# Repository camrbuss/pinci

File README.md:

# pinci the keyboard 🦐

*pinci pinches panic like popcorn*

This project is still under development, submit an issue if you have questions.

## Hardware

- 34 key layout with two thumb keys skewed outward
- [Kailh PG1232](https://www.kailhswitch.com/news/pg1232-keyboard-switch-brief-introduction-21834938.html) Low Profile Switches
- [Raspberry Pi Pico](https://www.raspberrypi.org/products/raspberry-pi-pico/) (RP2040)
- Reversible PCB
- TRS capable hardware (normal headphone cable)
- Minimal SMD components and no THT components
- No diodes, just direct switch to gpio connections
- Useable with and without a case

### BOM

| Part | Qty | Manufacturer Part No |
| ---- | --- | -------------------- |
| Kailh Swithces | 34 | PG1232 |
| Raspberry Pi Pico | 2 | SC0915 |
| 1206 5% 10k Ohm Resistor | 2 | N/A |
| 3.5mm Headphone Jack | 2 | 54-00177 |

## Firmware

The [firmware](https://github.com/camrbuss/pinci/blob/main/firmware/src/main.rs) is writen in Rust using the following (and more) libraries

- [Keyberon](https://github.com/TeXitoi/keyberon)
- [RTIC](https://github.com/rtic-rs/cortex-m-rtic)
- [rp2040-hal](https://github.com/rp-rs/rp-hal/tree/main/rp2040-hal)

## Inspiration

Thanks to all the open-source projects that have inspired this project

- [Ferris](https://github.com/pierrechevalier83/ferris)
- [Fifi](https://github.com/raychengy/fifi_split_keeb)
- [KeySeeBee](https://github.com/TeXitoi/keyseebee)

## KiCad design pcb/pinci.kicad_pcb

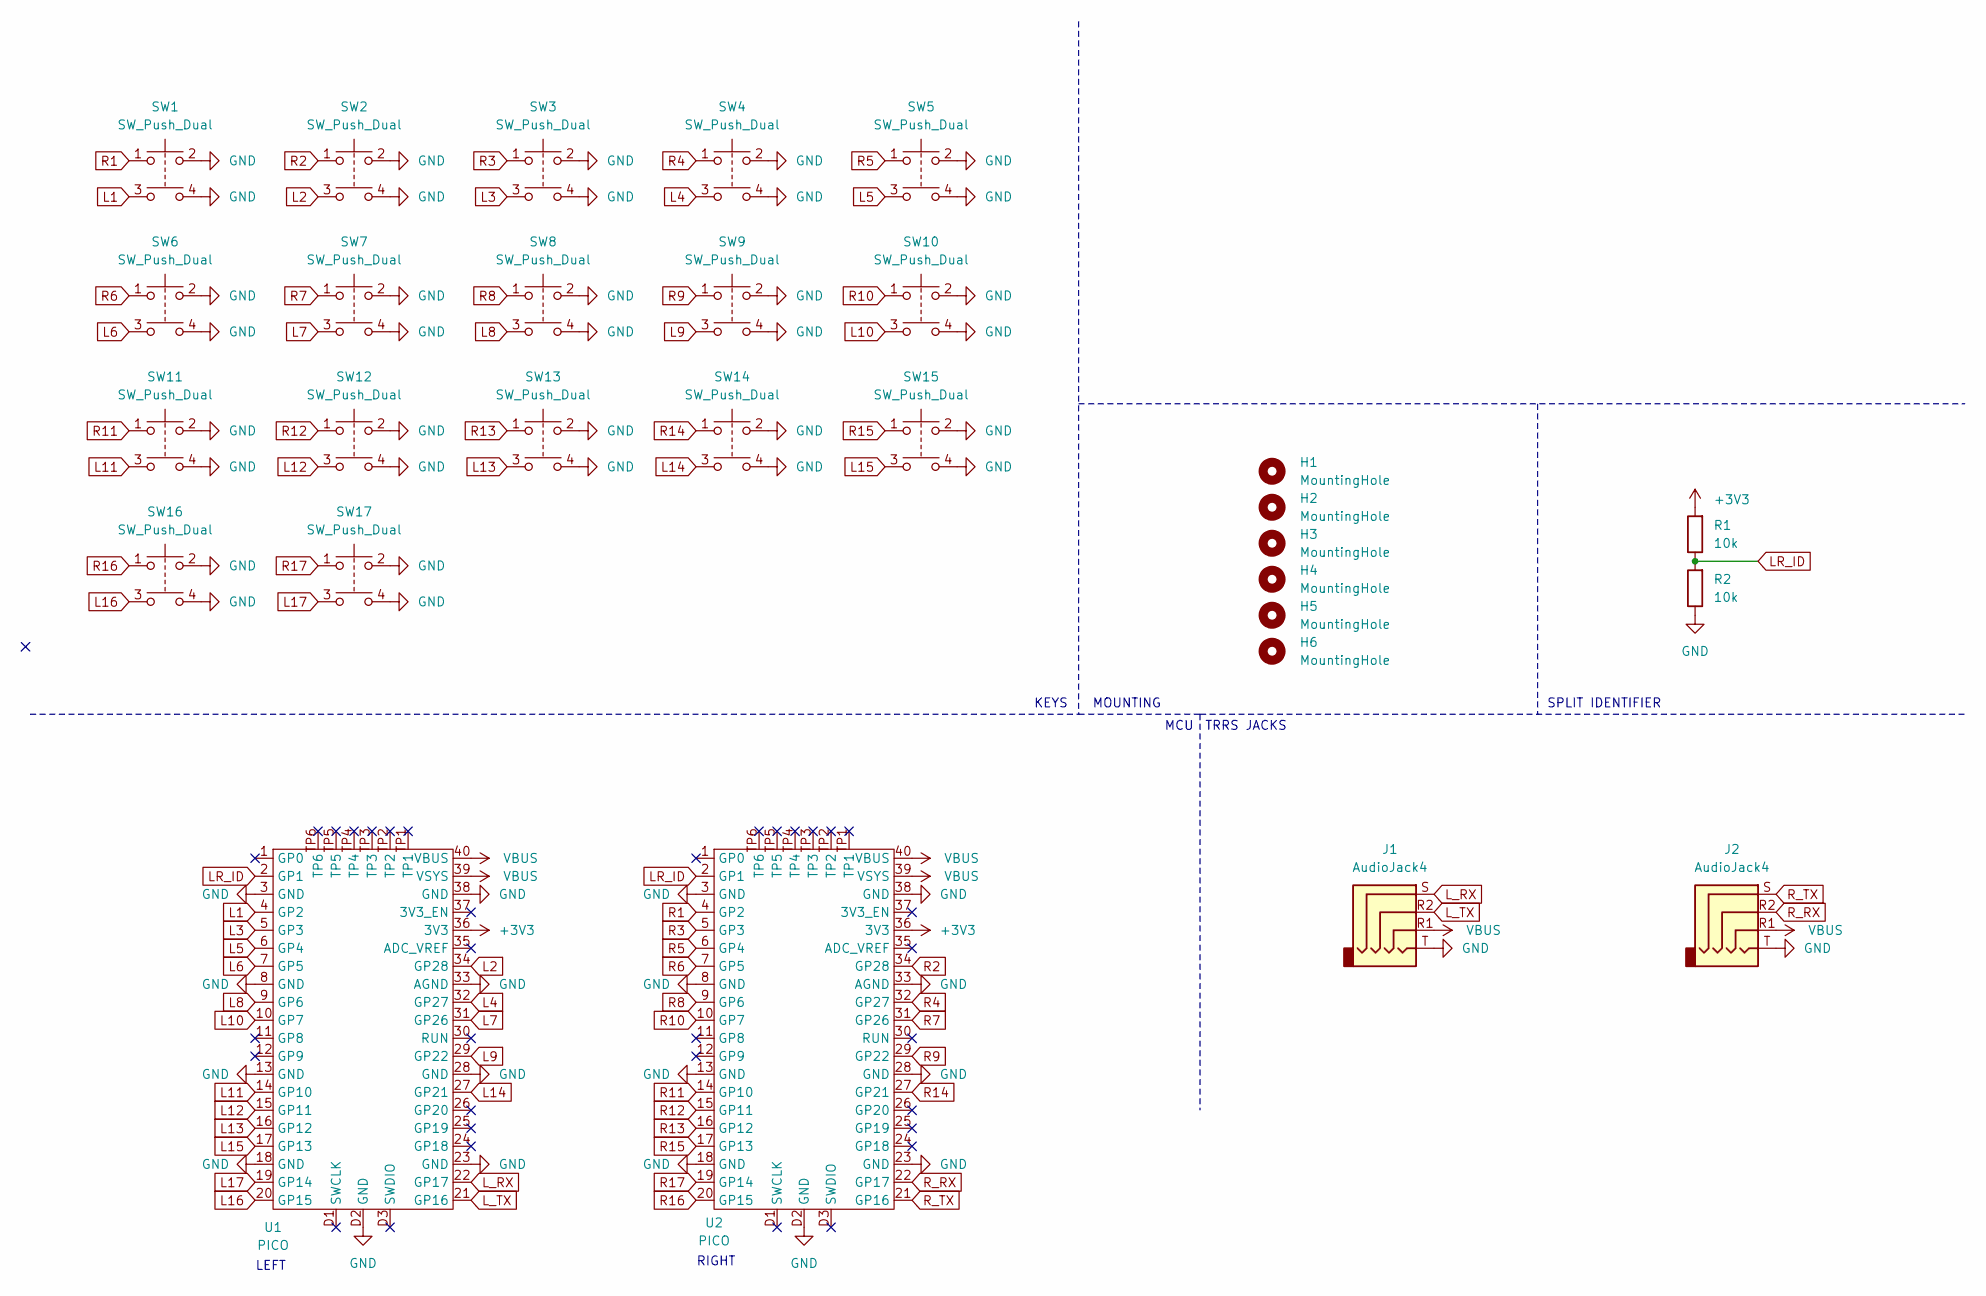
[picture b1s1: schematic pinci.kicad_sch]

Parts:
H1, H2: MountingHole; 90611A112_Screw_Mount_Nut
H3, H4, H5, H6: MountingHole; M2_Hole
J1, J2: AudioJack4; TRRS_Socket_54-00177
R1, R2: 10k; R_1206_3216Metric_Pad1.30x1.75mm_HandSolder
SW1, SW2, SW3, SW4, SW5, SW6, SW7, SW8, SW9, SW10, SW11, SW12, SW13, SW14, SW15, SW16, SW17: SW_Push_Dual; Kailh_PG1232
U1, U2: PICO; raspberrypi_pico

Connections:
+3V3: R1.2, U1.36 (3V3), U2.36 (3V3)
GND: J1.T, J2.T, R2.1, SW1.2, SW1.4, SW2.2, SW2.4, SW3.2, SW3.4, SW4.2, SW4.4, SW5.2, SW5.4, SW6.2, SW6.4, SW7.2, SW7.4, SW8.2, SW8.4, SW9.2, SW9.4, SW10.2, SW10.4, SW11.2, SW11.4, SW12.2, SW12.4, SW13.2, SW13.4, SW14.2, SW14.4, SW15.2, SW15.4, SW16.2, SW16.4, SW17.2, SW17.4, U1.3 (GND), U1.8 (GND), U1.13 (GND), U1.18 (GND), U1.23 (GND), U1.28 (GND), U1.33 (AGND), U1.38 (GND), U1.D2 (GND), U2.3 (GND), U2.8 (GND), U2.13 (GND), U2.18 (GND), U2.23 (GND), U2.28 (GND), U2.33 (AGND), U2.38 (GND), U2.D2 (GND)
L1: SW1.3, U1.4 (GP2)
L2: SW2.3, U1.34 (GP28)
L3: SW3.3, U1.5 (GP3)
L4: SW4.3, U1.32 (GP27)
L5: SW5.3, U1.6 (GP4)
L6: SW6.3, U1.7 (GP5)
L7: SW7.3, U1.31 (GP26)
L8: SW8.3, U1.9 (GP6)
L9: SW9.3, U1.29 (GP22)
L10: SW10.3, U1.10 (GP7)
L11: SW11.3, U1.14 (GP10)
L12: SW12.3, U1.15 (GP11)
L13: SW13.3, U1.16 (GP12)
L14: SW14.3, U1.27 (GP21)
L15: SW15.3, U1.17 (GP13)
L16: SW16.3, U1.20 (GP15)
L17: SW17.3, U1.19 (GP14)
LR_ID: R1.1, R2.2, U1.2 (GP1), U2.2 (GP1)
L_RX: J1.S, U1.22 (GP17)
L_TX: J1.R2, U1.21 (GP16)
R1: SW1.1, U2.4 (GP2)
R2: SW2.1, U2.34 (GP28)
R3: SW3.1, U2.5 (GP3)
R4: SW4.1, U2.32 (GP27)
R5: SW5.1, U2.6 (GP4)
R6: SW6.1, U2.7 (GP5)
R7: SW7.1, U2.31 (GP26)
R8: SW8.1, U2.9 (GP6)
R9: SW9.1, U2.29 (GP22)
R10: SW10.1, U2.10 (GP7)
R11: SW11.1, U2.14 (GP10)
R12: SW12.1, U2.15 (GP11)
R13: SW13.1, U2.16 (GP12)
R14: SW14.1, U2.27 (GP21)
R15: SW15.1, U2.17 (GP13)
R16: SW16.1, U2.20 (GP15)
R17: SW17.1, U2.19 (GP14)
R_RX: J2.R2, U2.22 (GP17)
R_TX: J2.S, U2.21 (GP16)
VBUS: J1.R1, J2.R1, U1.39 (VSYS), U1.40 (VBUS), U2.39 (VSYS), U2.40 (VBUS)

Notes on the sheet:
LEFT
RIGHT
KEYS
MOUNTING
MCU
TRRS JACKS
SPLIT IDENTIFIER

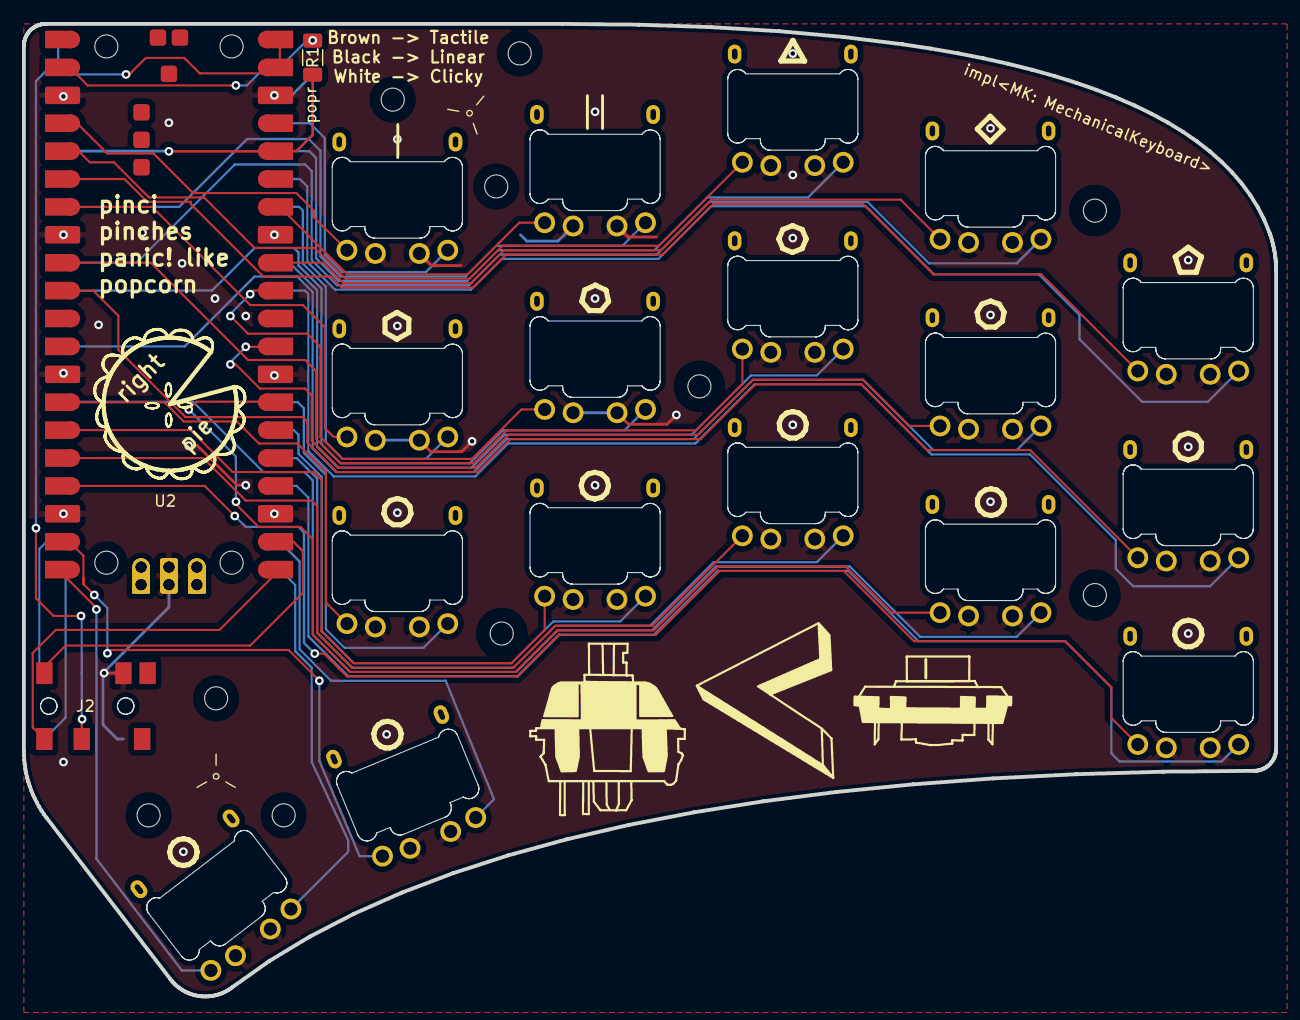
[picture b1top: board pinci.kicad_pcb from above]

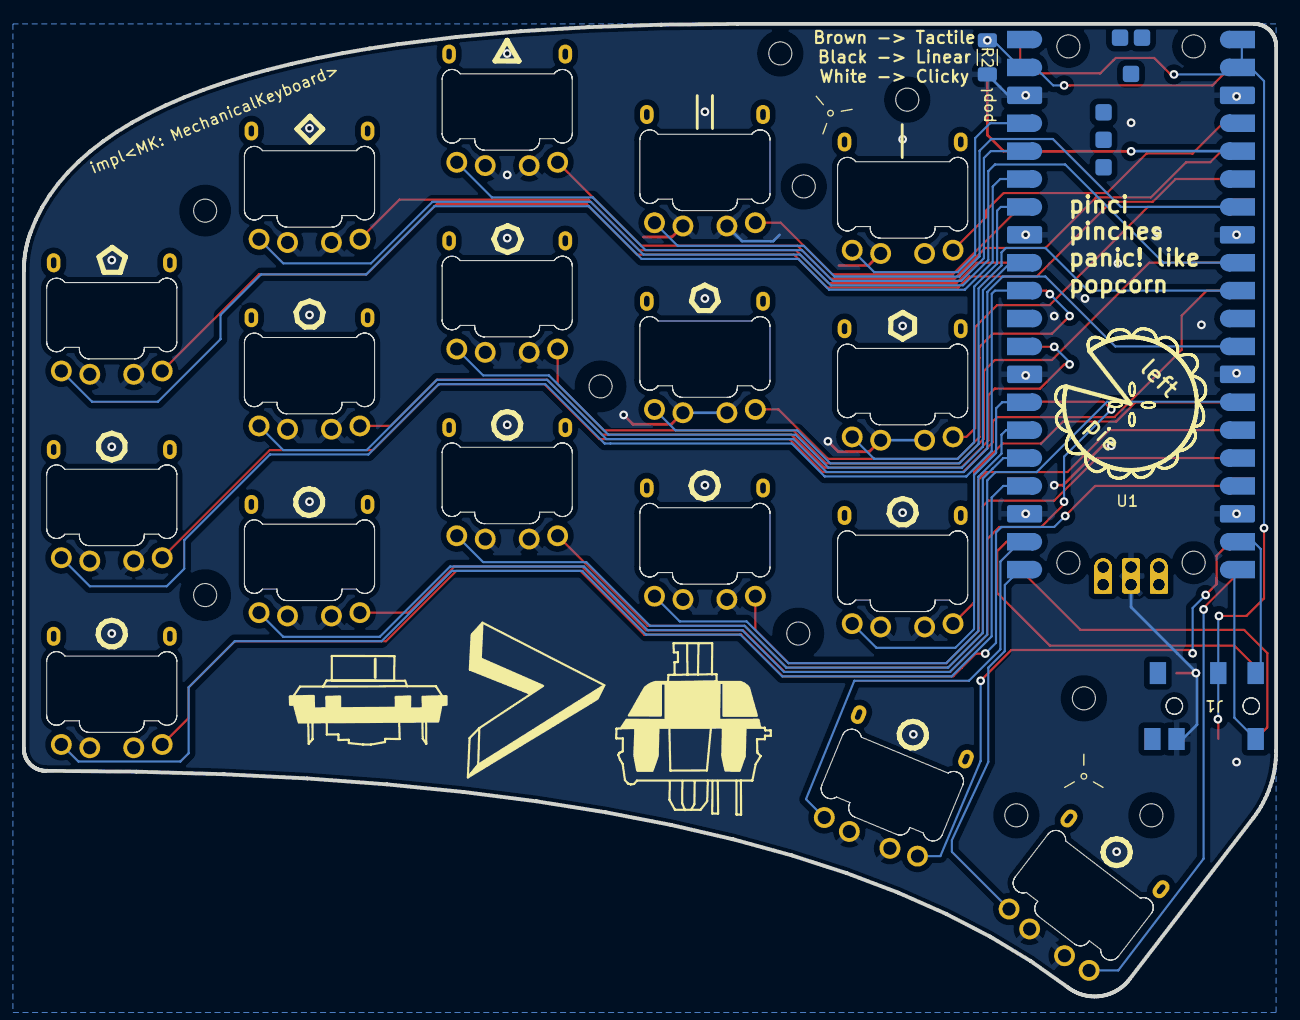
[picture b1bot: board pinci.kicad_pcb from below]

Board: 2 copper layers, 114.0 x 88.5 mm, 29 parts (5 on the bottom side), 42 nets.

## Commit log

2021-08-08 LICENSE
2021-08-09 board edge and silkscreen
2021-08-16 footprint positions prelim
2021-08-16 switches prelim routed
2021-08-17 routing rc
2021-08-17 drc fixes
2021-08-19 pinci pcb 0.1
2021-09-02 initial compiling firmware
2021-09-02 ps2 timing in pio
2021-09-11 usb enumeration a key presses
2021-09-11 left and right transform
2021-09-12 quasi split serial comms
2021-09-14 RTIC 0.6 with USB enumeration and scan
2021-09-26 Register level UART for split comms
2021-09-28 Watchdog and Uf2
2021-09-28 README Img update
2021-09-28 Complete photo
2021-10-02 Chording added
2021-10-02 Add BOM with part no's
2021-12-18 Updated all dependencies to their latest versions (where possible) and fixed the code to work with them. Also fixed Keberon dep inside Cargo.toml.
2021-12-19 timer hal
2022-08-20 updated dependencies
2023-01-05 Initial polling uart reat
2023-01-08 functional uart polling
2023-01-08 uart polling with good layout
